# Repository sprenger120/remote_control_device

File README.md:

# remote_control_device

Firmware, KiCAD files, 3D designes of an embedded STM32 based device I was commissioned to create for an autonomous bike. **Clone with --recursive**
It reads receives stick positions from a hobby remote control (FrSky based) and controls various actors around the bike. Also serves as a CANopen bus master, monitoring for timeouts and handling some safety aspects.   
The firmware is fully unit tested and fuzzed using American Fuzzy Lop. 

Remote control system for the autonomous bike(s) based on:
 
* FrSky's QX7 remote control
* FrSky's XM+ diversity, non-telemetry receiver
* OpenTX remote control firmware
* ST's NUCLEO-F302R8 board
* custom adapter board
* CANfestival CANopen stack
* STM32 Cube HAL 
* FreeRTOS 

### Project overview / folder stucture
<pre>
remote_control
|-- hardware*          **General information and assembly instructions**
|   |-- 3D             3D models of the units case
|   |-- datasheets     all relevant datasheets of components used in the custom adapter board
|   |-- adapterBoard   KiCAD 5 files
|   |   |-- bom        Interactive BOM for PCB assembly
|-- firmware*          **Code for the micro controller**
</pre>
\* contains extra readme

### General usage of remote control (radio)

Switch on the remote control by holding the center button for 2 seconds. The remote control device in the bike will be in *start* mode until radio link is engaged and all canbus devices area ready. Beware that getting **too close** to the antennas of the RDC with the radio will cause it to loose connection due to overload (the receiver is very sensitive).
The radio will start beeping if left untouched for more than 60 minutes or if the batteries get low. It will never shut off by itself and **will** kill the batteries if signals are ignored.   

To enable any mode the safety switch (momentary - will return to by it's own to default position) has to be flipped up **before** activating either of the two mode switches.
Remote mode will not activate if the throttle is raised. If two modes are activated at the same none will activate.

Emergency can be pressed at at any time. When inside remote or autonomous all switches have to be returned to idle to
leave emergency. Emergency will only be active for the duration of the button press when bike is idling.   

Manual mode overrides **all** control of the bike; even emergency. When exiting manual the bike will not be directly returning to the previous mode.  

### Remote control device LED codes
The LEDs of the device can be in the following states

- off/dim
- fast blinking
- on
- counting (blinking for *n* cycles, off for longer time, repeating)

##### Hardware LED

- off/dim: device is starting
- fast blinking:
    waiting for all canfestival nodes to start up
    no actor values will be sent until this is done
- on: (no errors)
- counting mode:
    - lower counts overwrite higher ones (lower = more important error)
    - 1 count: can network error
    - 2 count: brake heartbeat timeout
    - 3 count: steering timeout
    - 4 count: wheel motor timeout

##### Remote LED

- on: remote control connection established (no errors)
- fast blinking: manual mode (overwrites connection lost / established)
- off: connection lost

### Wiring of remote control device
Input voltage 6-24V (reverse polarity protected) or USB powered through nucleo. ESD protection only rudimentary due to layout error. 
Do not power up device without antennas attached it may shorten the lifespan of the receiver. Switch 01 = manual mode. Switch 02 = hard emergency. Just connect a switch, pull-up is provided by the board.

## Device pictures

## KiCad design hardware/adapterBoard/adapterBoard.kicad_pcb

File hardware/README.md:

# Hardware
- NUCLEO-64 with STM32F302R8 processor with a custom adapter board ontop 
- FrSky XM+ receiver module soldered to the adapter board
- FrSky QX7 remote control with custom emergency stop button and LiIon batteries
- Designed with KiCad 5

### Configuration of remote control
Settings applied to the remote control. You may use OpenTX Companion to copy the config from one radio to the next.

Radio Setup:

- set date, time
- set batt range 9,9-12.6
- batt low warning 10v
- inactivity 60min
- backlight mode: keys
- global functions:
  - 01: on, volume, Input11(s1), active

Setup:

- model name: bike 1
 - s-warning: a,b deactivated
 - internal rf
   - d16
   - ch1-16
   - rx num 1
   - binding:  ch1-8 telem on
   - failsafe: no pulses
- inputs: T, A, E, R, SA, SB, SC, SD, SH, SF, S1, S2, MAX, MAX, MAX, MAX
 - SA input weight -100, offset -100
- mixer click every entry once to assign input
- logical switches
  - 01: a>x, SC, -50
  - 02: a>x, SD, -50
  - 03: AND, L01, L02
- special functions:
  - 01: L03, play sound, wrn1, 1 
  - 02: SA half, play sound, wrn2, -

### Modification of remote control
Opened the unit and removed switch SA and replaced it with a pushbutton. Original hole needs to be enlarged with a drill.

### adapterBoard v1 PCB  Notes
- Buck converter feedback resistive divider component R7 should be 52.3K instead of 52.3R (installed 51K as substitute), corrected in schematic
- XM+ receiver power switch is correctly denoted as normally closed, normally open was accidentally bought, removed SW1 and bridged pads so receiver is always on
- 10uF MLCC were specified as 1210 (imp.) components, 1206 (imp.) were bought, installed 1206 components without issue
- D-SUB connector needs to be soldered to bottom layer because of accidental pinout mirroring
- Modifications to Nucleo board so PCB fits ontop for soldering
   - Snip off Arduino headers on both sides
   - Remove User and Reset button caps and snip button stem even with button casing 
   - Snip off two pin header with jumpers and solder bridges so originl configuration with jumpers is estabilished
- "debugUART" (USART1) and XM+ USART (USART2) need to be switched because the built-in STLinks UART converter is connected to USART2
to achive this the following was done
  - SB14, SB13 resistors have been removed
  - wiring from USART1's pins has been added to the STLinks side of the resistors
- Removed U2 as it is used incorrectly and bridges SW01 and SW02

### Assembly
- assemble adapter board according to interactive bom in adapterBoard/bom
- don't forget to do the buck converter and switch fixes mentioned above
- solder on the XM+ with the help of 3x1 Dupont pin header
- remove original antennas very carefully (do not pull straight up but use a lever below the crimp to pry it off)
- attach the two MHF4 -> RP-SMA adapter cables
- 3D print enclosure (3D folder, [online cad](https://cad.onshape.com/documents/3ef6522cbbdee6598b7177e3/w/a3b5db2935905c5482c54099/e/5c57edc258b28d56febac476)) 
- do modifications to the nucleo board as seen above
- slot adapter board onto nucleo and use nylon standoff to reeinforce connection between the two boards
- screw in the RP-SMA terminals while only using the plain washer but not the split ring
- insert the board into the enclosure and use three M3 screws with appropriate length (25mm) to fasten the board stack to the enclosure
- fasten the enclosure's top with small short wood screws
- flash the latest firmware

### External resources other than datasheets
* [ST Nucleo64 footprint](https://github.com/mobilinkd/stm-morpho-template)

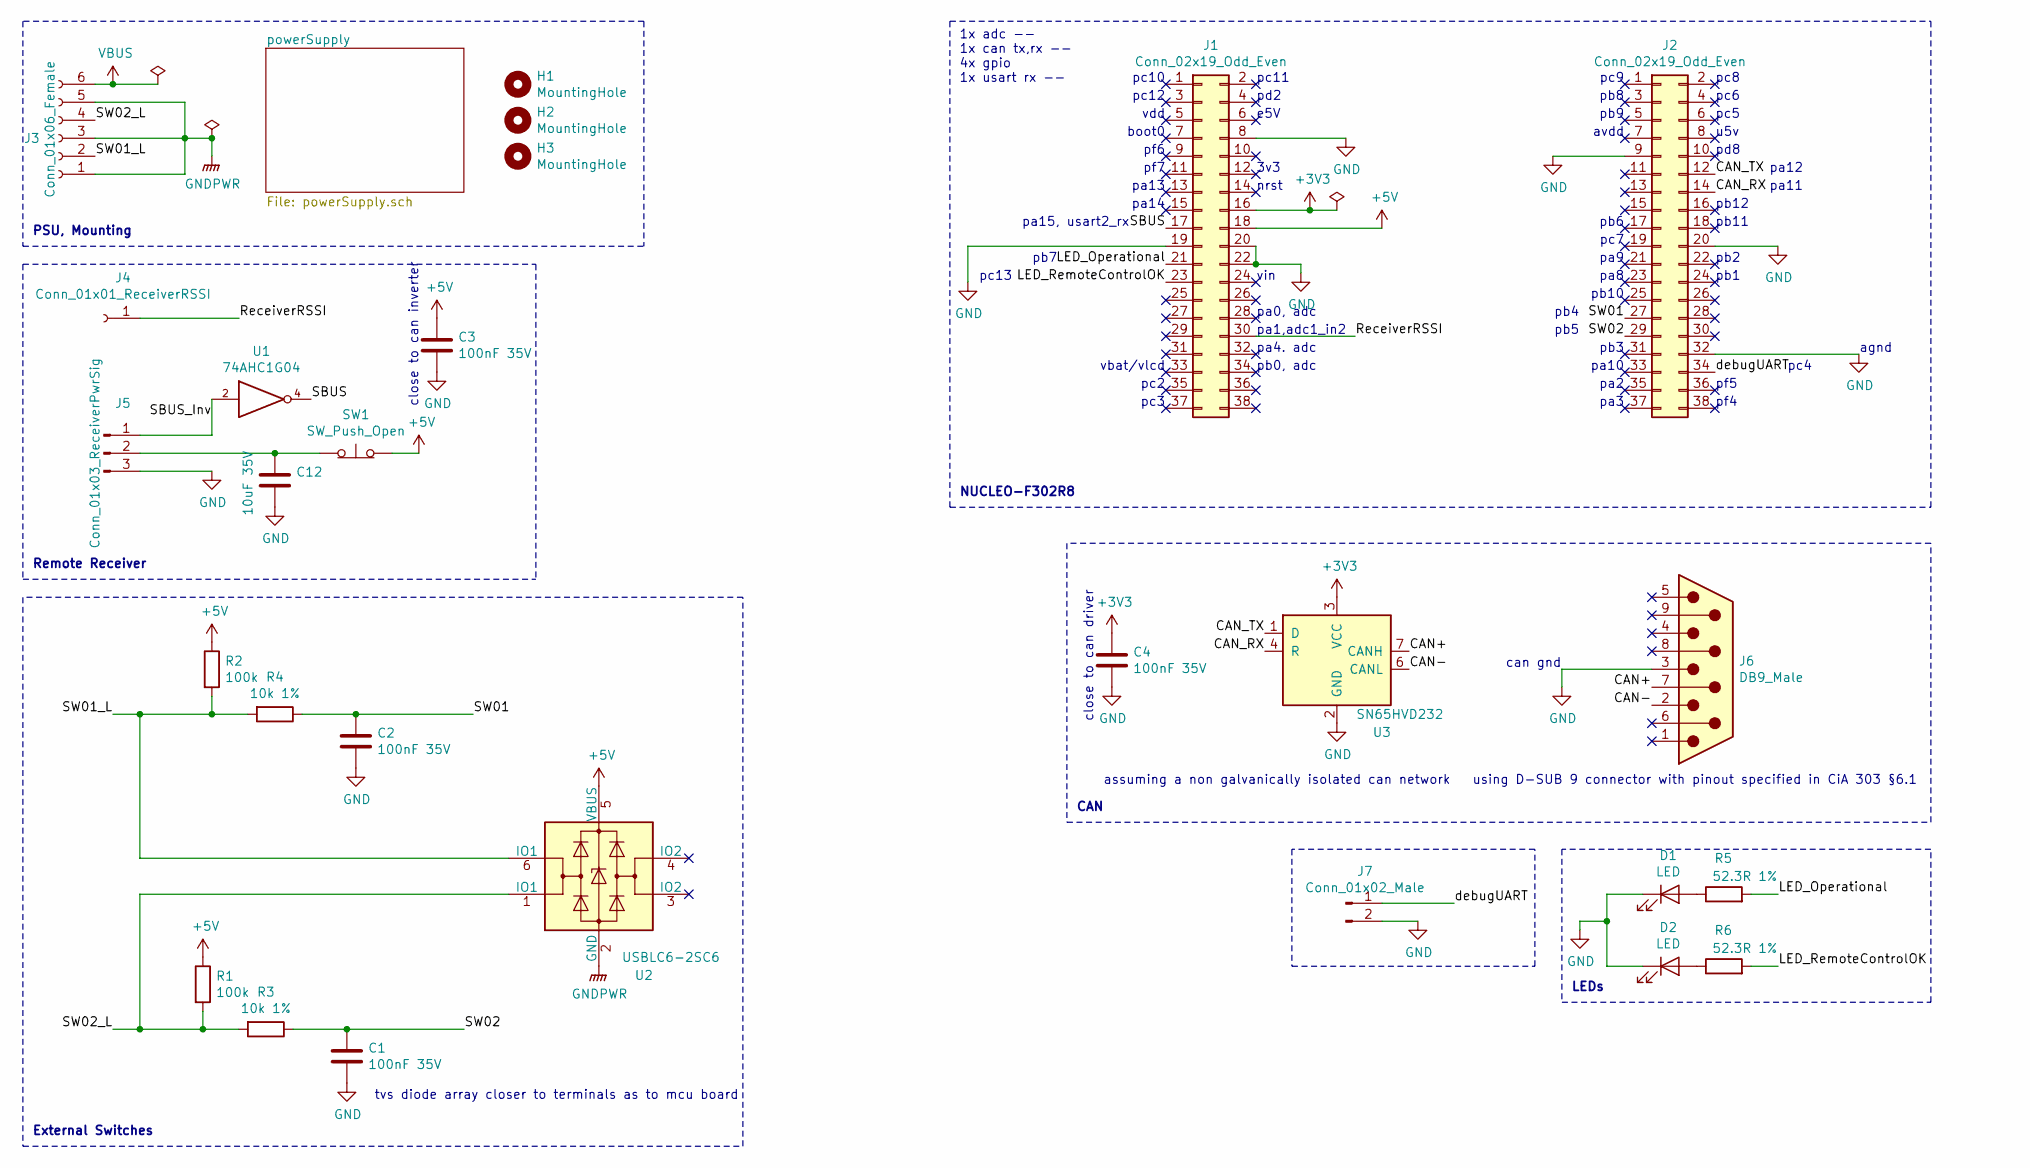
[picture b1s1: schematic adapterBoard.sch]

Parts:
C1, C2, C3, C4: 100nF 35V; C_0603_1608Metric
C12: 10uF 35V; C_1210_3225Metric
D1, D2: LED; LED_D3.0mm
H1, H2, H3: MountingHole; MountingHole_3mm
J1, J2: Conn_02x19_Odd_Even; PinSocket_2x19_P2.54mm_Vertical
J3: Conn_01x06_Female; TerminalBlock_Phoenix_PT-1,5-6-5.0-H_1x06_P5.00mm_Horizontal
J4: Conn_01x01_ReceiverRSSI; TestPoint_Pad_2.0x2.0mm
J5: Conn_01x03_ReceiverPwrSig; PinSocket_1x03_P2.54mm_Vertical
J6: DB9_Male; DSUB-9_Male_Horizontal_P2.77x2.84mm_EdgePinOffset9.90mm_Hou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
J7: Conn_01x02_Male; PinSocket_1x02_P2.54mm_Vertical
R1, R2: 100k; R_0603_1608Metric
R3, R4: 10k 1%; R_0603_1608Metric
R5, R6: 52.3R 1%; R_0603_1608Metric
SW1: SW_Push_Open; alps_SKRPASE010
U1: 74AHC1G04; SOT-353_SC-70-5
U2: USBLC6-2SC6; SOT-23-6
U3: SN65HVD232; SOIC-8_3.9x4.9mm_P1.27mm

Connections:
+3V3: C4.1, J1.16, U3.3 (VCC)
+5V: C3.1, J1.18, R1.1, R2.1, SW1.2 (B), U1.5 (VCC), U2.5 (VBUS); also elsewhere on the board
/CAN+: J6.7, U3.7 (CANH)
/CAN-: J6.2, U3.6 (CANL)
/CAN_RX: J2.14, U3.4 (R)
/CAN_TX: J2.12, U3.1 (D)
/LED_Operational: J1.21, R5.2
/LED_RemoteControlOK: J1.23, R6.2
/ReceiverRSSI: J1.30, J4.1
/SBUS: J1.17, U1.4
/SBUS_Inv: J5.1, U1.2
/SW01: C2.1, J2.27, R4.1
/SW01_L: J3.2, R2.2, R4.2, U2.6 (IO1)
/SW02: C1.1, J2.29, R3.1
/SW02_L: J3.4, R1.2, R3.2, U2.1 (IO1)
/debugUART: J2.34, J7.1
GND: C1.2, C2.2, C3.2, C4.2, C12.2, D1.1 (K), D2.1 (K), J1.8, J1.19, J1.20, J1.22, J2.9, J2.20, J2.32, J5.3, J6.3, J7.2, U1.3 (GND), U3.2 (GND); also elsewhere on the board
GNDPWR: J3.1, J3.3, J3.5, U2.2 (GND); also elsewhere on the board
unnamed: C12.1, J5.2, SW1.1 (A)
unnamed: D1.2 (A), R5.1
unnamed: D2.2 (A), R6.1
VBUS: J3.6; also elsewhere on the board

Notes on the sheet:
vdd
boot0
vbat/vlcd
e5V
close to can driver
tvs diode array closer to terminals as to mcu board
assuming a non galvanically isolated can network
using D-SUB 9 connector with pinout specified in CiA 303 §6.1
can gnd
NUCLEO-F302R8
CAN
LEDs
Remote Receiver
PSU, Mounting
External Switches
close to can inverter
1x adc -- 1x can tx,rx -- 4x gpio 1x usart rx --
nrst
3v3
vin
pc4
pa15, usart2_rx
pc10
pc12
pf6
pf7
pa13
pa14
pb7
pc13
pc2
pc3
pc11
pd2
pa0, adc
pa1,adc1_in2
pa4. adc
pb0, adc
pc9
pb8

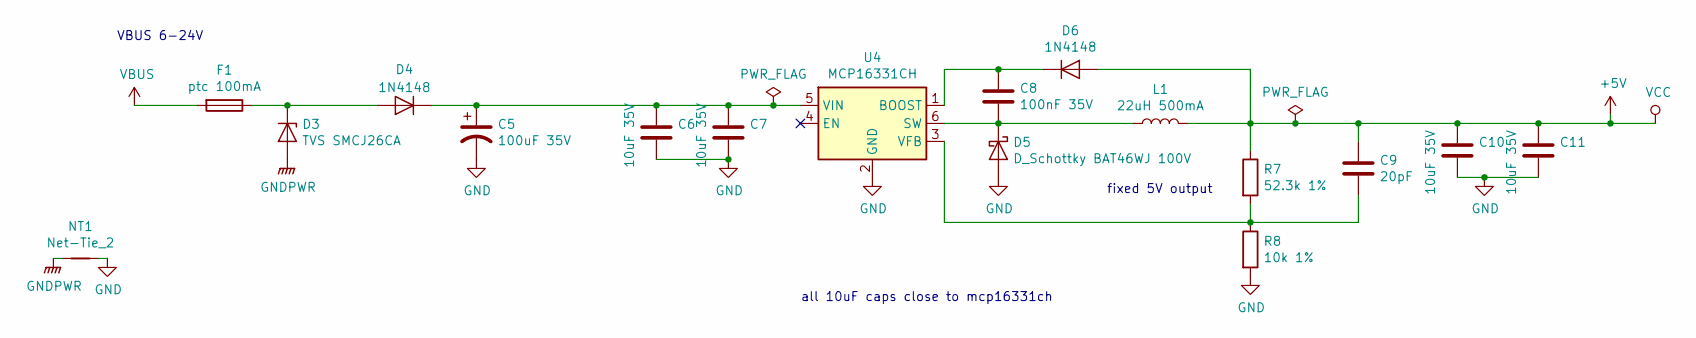
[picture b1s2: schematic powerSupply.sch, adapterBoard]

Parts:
C5: 100uF 35V; CP_Elec_10x10.5
C6, C7, C10, C11: 10uF 35V; C_1210_3225Metric
C8: 100nF 35V; C_0603_1608Metric
C9: 20pF; C_0603_1608Metric
D3: TVS SMCJ26CA; D_SMC
D4, D6: 1N4148; D_DO-35_SOD27_P7.62mm_Horizontal
D5: D_Schottky BAT46WJ 100V; D_SOD-323F
F1: ptc 100mA; Fuse_1206_3216Metric
L1: 22uH 500mA; L_Taiyo-Yuden_NR-40xx
NT1: Net-Tie_2; NetTie-2_SMD_Pad2.0mm
R7: 52.3k 1%; R_0603_1608Metric
R8: 10k 1%; R_0603_1608Metric
U4: MCP16331CH; SOT-23-6

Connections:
+5V: C9.1, C10.1, C11.1, D6.2 (A), L1.2, R7.1; also elsewhere on the board
GND: C5.2, C6.2, C7.2, C10.2, C11.2, D5.2 (A), NT1.2, R8.2, U4.2 (GND); also elsewhere on the board
GNDPWR: D3.2 (A), NT1.1; also elsewhere on the board
unnamed: C5.1, C6.1, C7.1, D4.1 (K), U4.5 (VIN)
unnamed: C8.1, D6.1 (K), U4.1 (BOOST)
unnamed: C8.2, D5.1 (K), L1.1, U4.6 (SW)
unnamed: C9.2, R7.2, R8.1, U4.3 (VFB)
unnamed: D3.1 (K), D4.2 (A), F1.1
VBUS: F1.2; also elsewhere on the board

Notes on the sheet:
fixed 5V output
all 10uF caps close to mcp16331ch
VBUS 6-24V

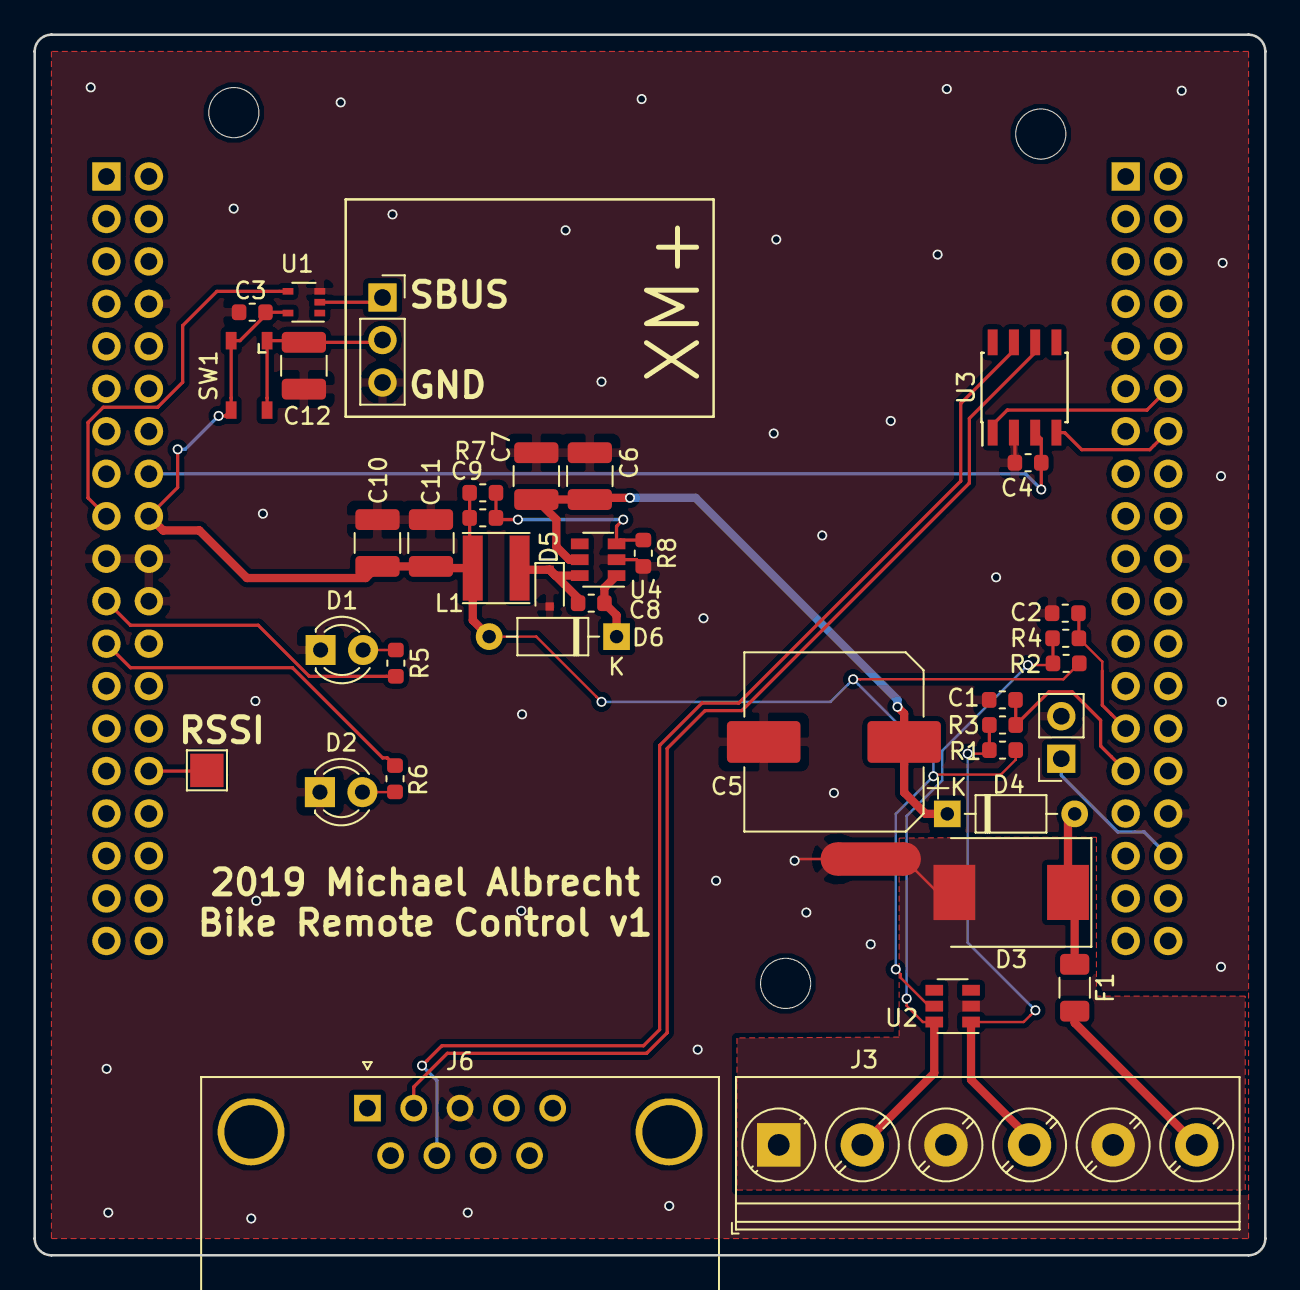
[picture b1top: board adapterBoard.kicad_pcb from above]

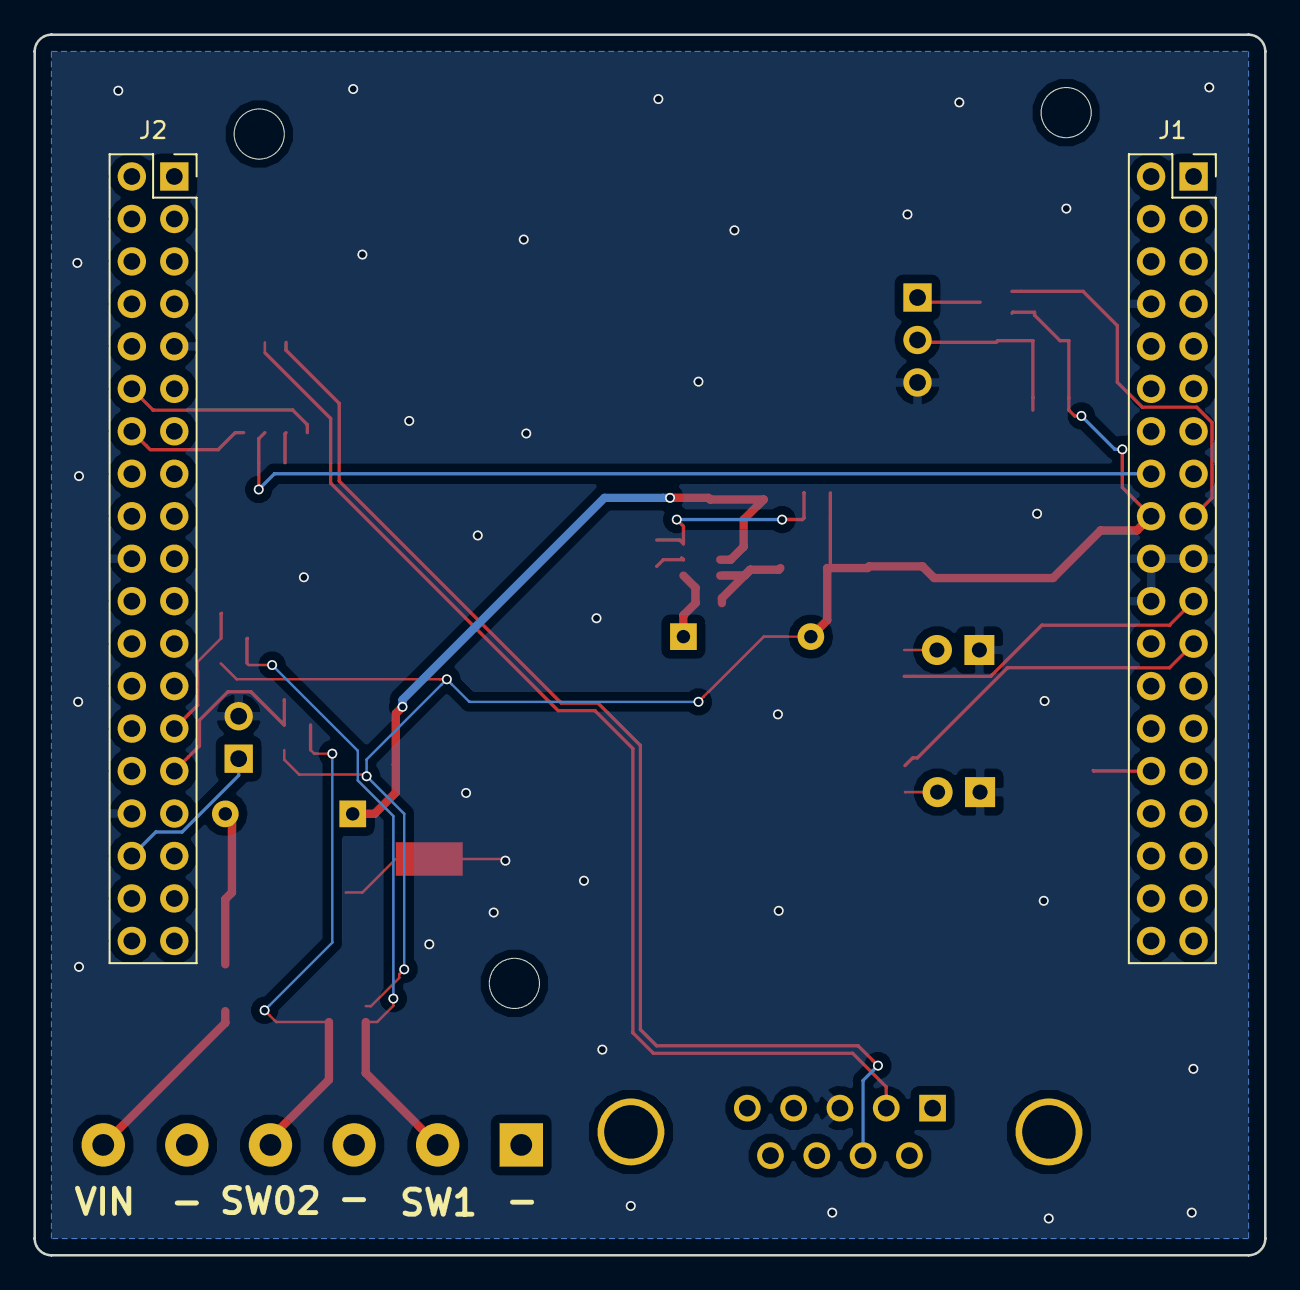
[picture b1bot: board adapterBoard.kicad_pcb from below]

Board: 2 copper layers, 73.6 x 73.0 mm, 44 parts (2 on the bottom side), 27 nets.

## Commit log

2021-01-26 Added project
2021-01-26 Added readme
2021-01-26 Update README.md
    Fixed image links
2021-01-28 Added task that constantly hashes firmware Added script that can inject a precomputed firmware hash
2021-03-11 Added wip cmake build code
